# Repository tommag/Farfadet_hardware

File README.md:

# Farfadet Hardware

This repo contains KiCad EDA files for the Farfadet modular motor system.

You can check some info on the project here : <https://hackaday.io/project/45995-farfadet>

Each folder here contains a different hardware project. There is a schematic export in PDF format for each project. You can find the gerber files in the `gerber` directories. The Bill of Materials and component placement files are in the `production` directories. 

## License
This project is Open Source Hardware, licensed under the Creative Commons BY-SA 4.0 license. You can find the full license text here : <https://creativecommons.org/licenses/by-sa/4.0/>

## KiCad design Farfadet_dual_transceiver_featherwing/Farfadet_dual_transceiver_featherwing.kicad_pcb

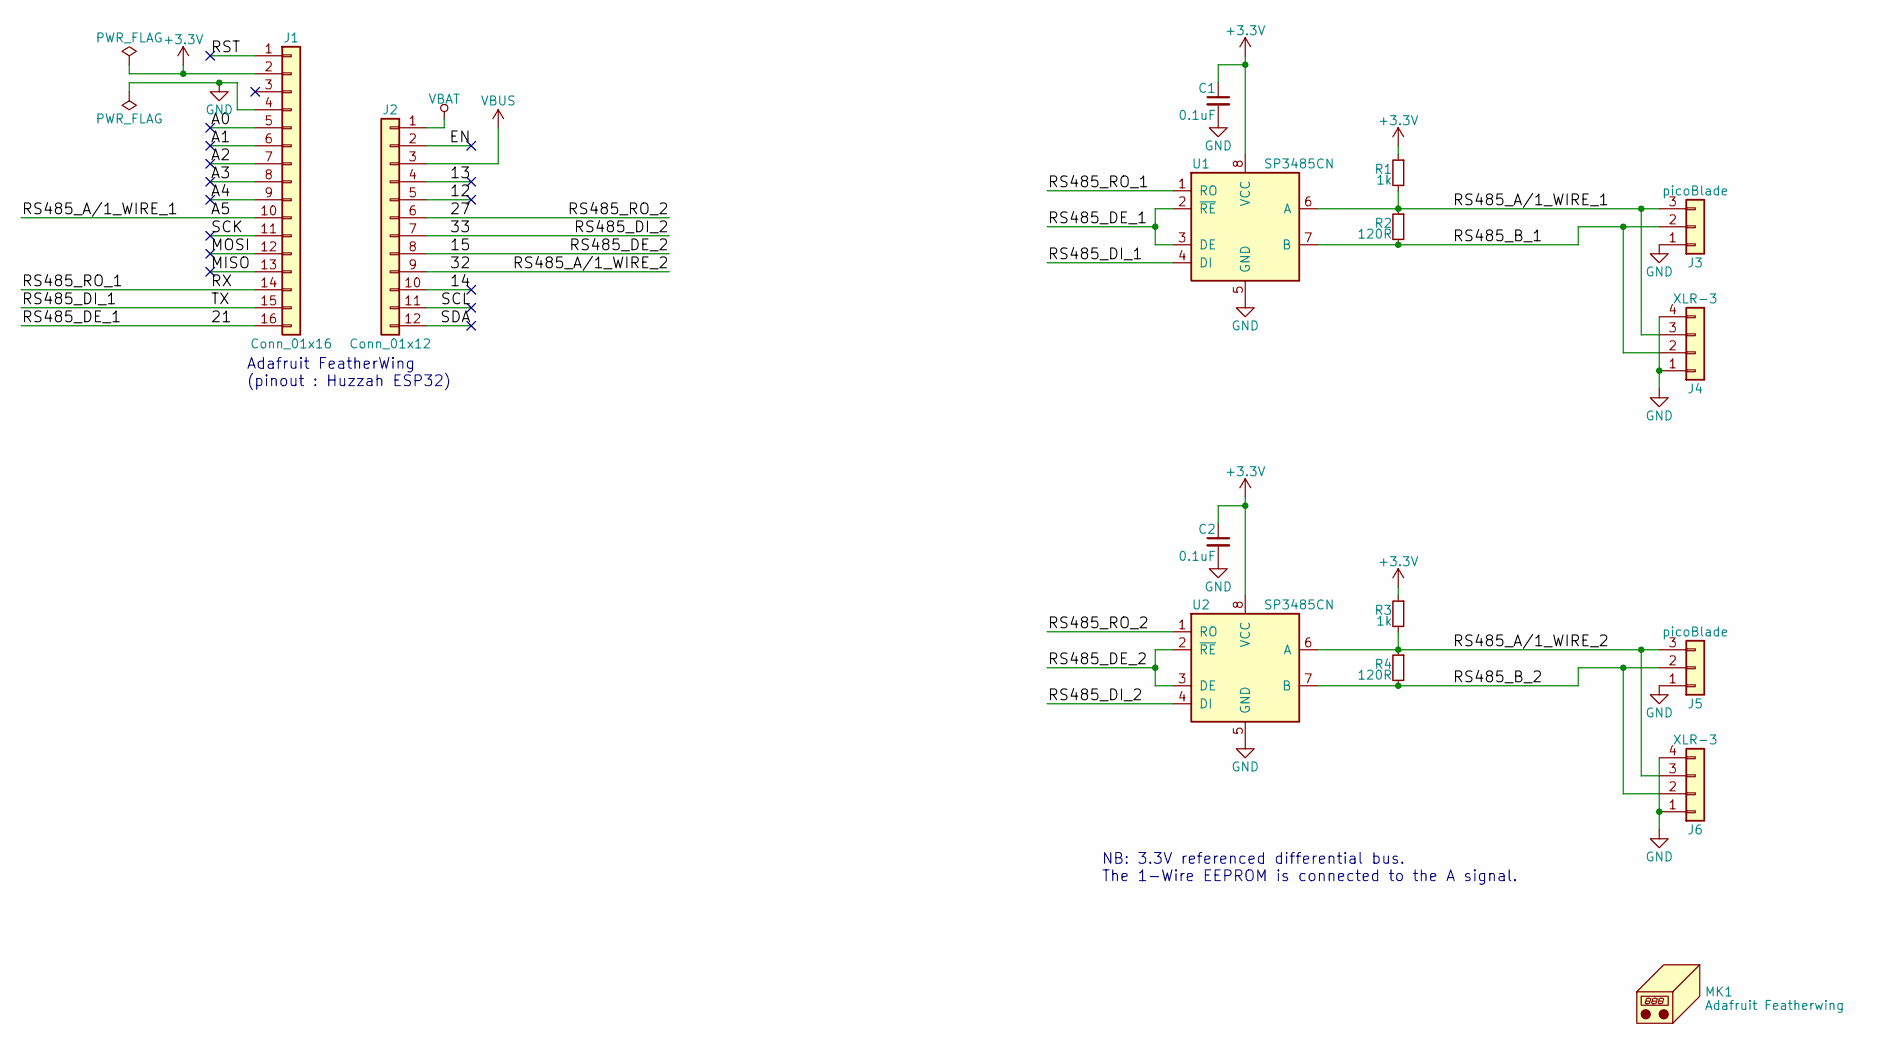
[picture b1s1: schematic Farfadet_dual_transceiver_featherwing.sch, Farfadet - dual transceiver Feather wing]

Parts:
C1, C2: 0.1uF; C_0603
J1: Conn_01x16; Pin_Header_Straight_1x16_Pitch2.54mm
J2: Conn_01x12; Pin_Header_Straight_1x12_Pitch2.54mm
J3, J5: picoBlade; Molex_PicoBlade_53047-0310_03x1.25mm_Straight
J4, J6: XLR-3; Neutrik_XLR_NC3FAAH2
MK1: Adafruit Featherwing; PCB_FeatherWing
R1, R3: 1k; R_0603
R2, R4: 120R; R_0603
U1, U2: SP3485CN; SOIC-8_3.9x4.9mm_Pitch1.27mm

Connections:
+3V3: C1.1, C2.1, J1.2, R1.1, R3.1, U1.8 (VCC), U2.8 (VCC)
/12: J2.5
/13: J2.4
/14: J2.10
/15: J2.8, U2.2 (~RE~), U2.3 (DE)
/21: J1.16, U1.2 (~RE~), U1.3 (DE)
/27: J2.6, U2.1 (RO)
/32: J2.9, J5.3, J6.3, R3.2, R4.1, U2.6 (A)
/33: J2.7, U2.4 (DI)
/A0: J1.5
/A1: J1.6
/A2: J1.7
/A3: J1.8
/A4: J1.9
/A5: J1.10, J3.3, J4.3, R1.2, R2.1, U1.6 (A)
/EN: J2.2
/MISO: J1.13
/MOSI: J1.12
/RS485_B_1: J3.2, J4.2, R2.2, U1.7 (B)
/RS485_B_2: J5.2, J6.2, R4.2, U2.7 (B)
/RS485_DI_1: J1.15, U1.4 (DI)
/RS485_RO_1: J1.14, U1.1 (RO)
/RST: J1.1
/SCK: J1.11
/SCL: J2.11
/SDA: J2.12
GND: C1.2, C2.2, J1.4, J3.1, J4.1, J4.4, J5.1, J6.1, J6.4, U1.5 (GND), U2.5 (GND)
VBAT: J2.1
VBUS: J2.3

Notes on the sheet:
Adafruit FeatherWing (pinout : Huzzah ESP32)
NB: 3.3V referenced differential bus. The 1-Wire EEPROM is connected to the A signal.

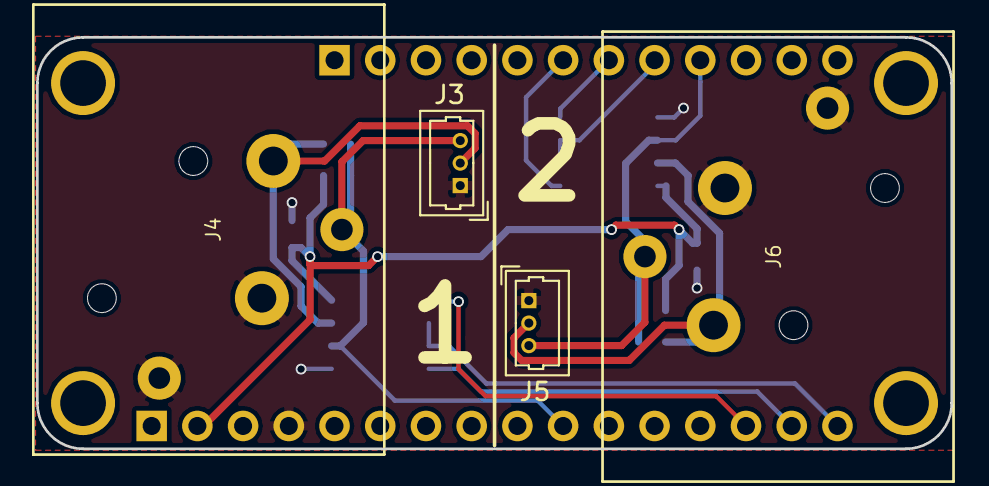
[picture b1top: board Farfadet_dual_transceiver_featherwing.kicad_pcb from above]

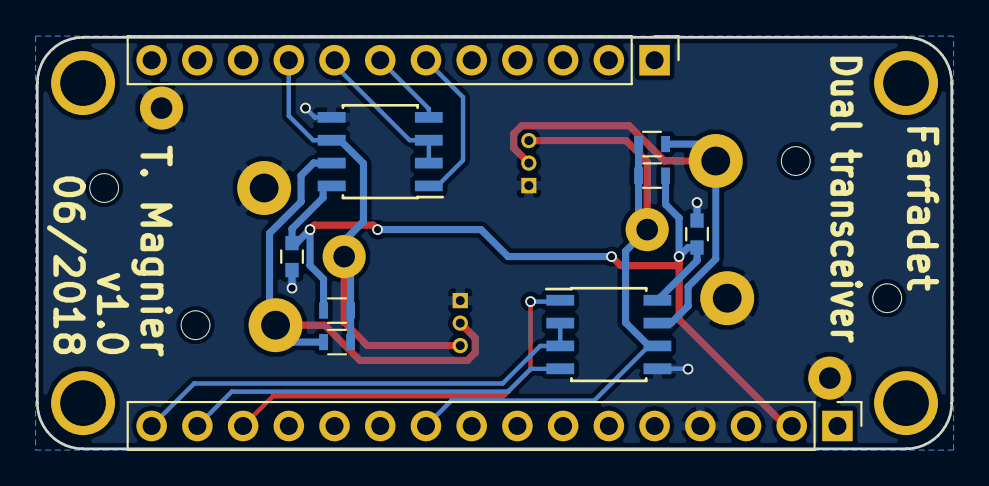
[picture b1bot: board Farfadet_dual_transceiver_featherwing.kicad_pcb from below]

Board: 2 copper layers, 50.8 x 22.9 mm, 15 parts (10 on the bottom side), 12 nets.

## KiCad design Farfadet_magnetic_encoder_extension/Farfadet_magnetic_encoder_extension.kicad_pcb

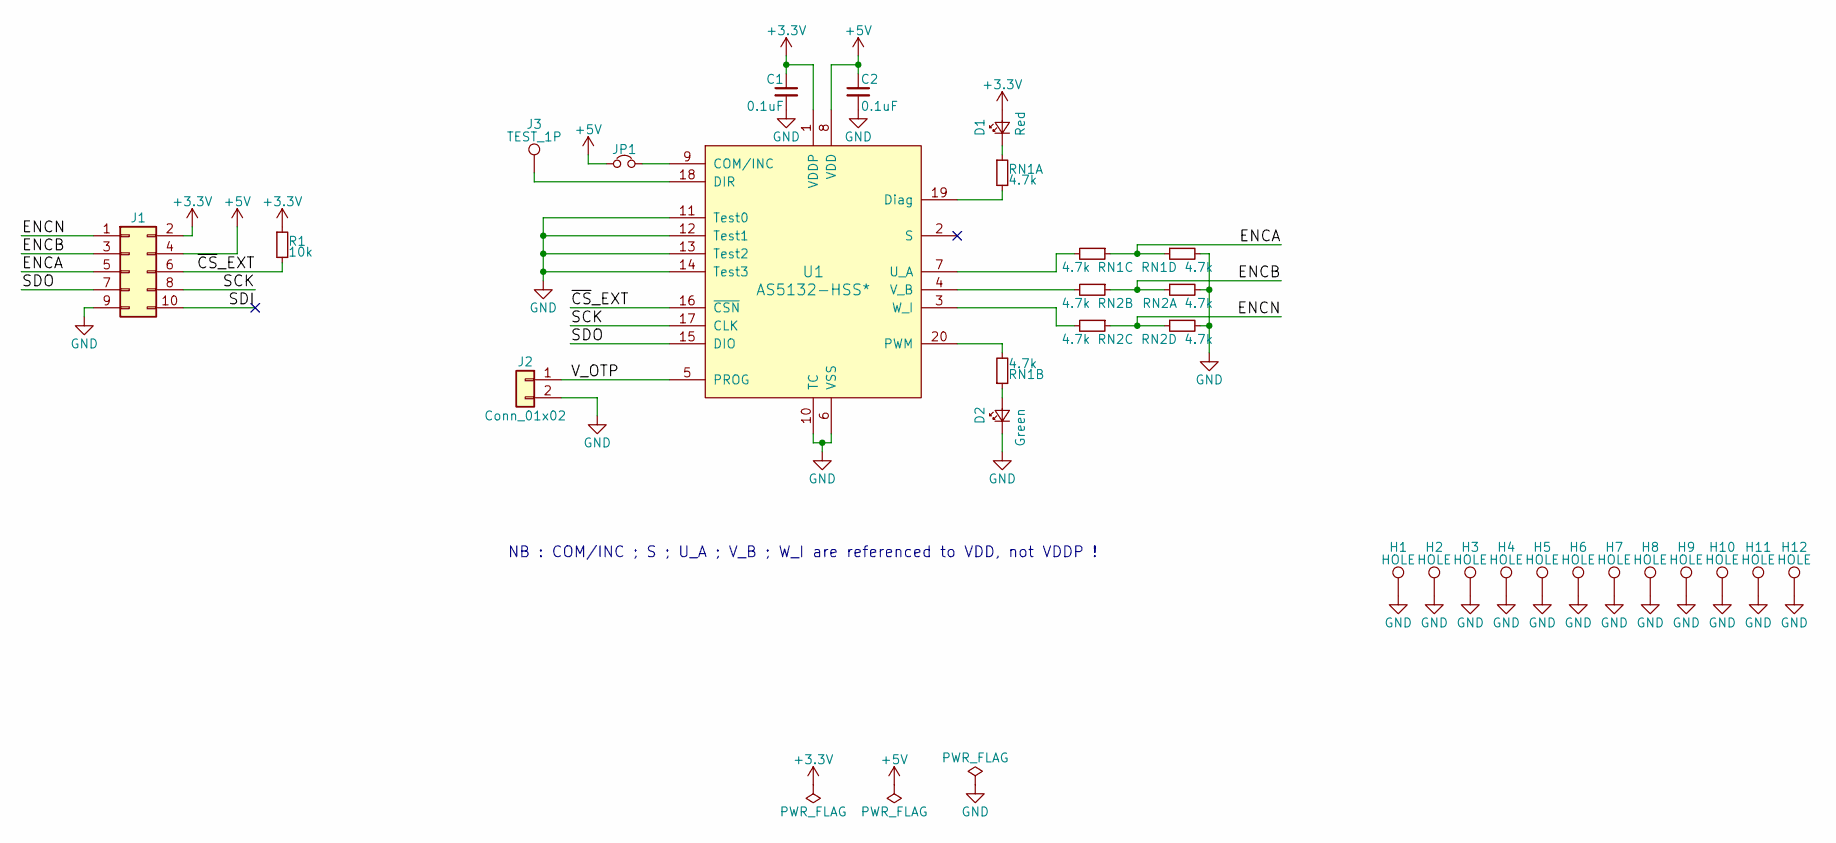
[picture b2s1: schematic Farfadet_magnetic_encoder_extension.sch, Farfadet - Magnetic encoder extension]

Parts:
C1, C2: 0.1uF; C_0603
D1: Red; LED_0603
D2: Green; LED_0603
H1, H2, H3, H4, H5, H6, H7, H8, H9, H10, H11, H12: HOLE; MountingHole_3.2mm_M3_Pad_Via
J1: Conn_02x05_Odd_Even; Socket_Strip_Straight_2x05_Pitch1.27mm_SMD
J2: Conn_01x02; Test_Point_2Pads
J3: TEST_1P; Measurement_Point_Round-TH_Small
JP1: Jumper_NC_Small; Solder_Jumper_2_conn
R1: 10k; R_0603
RN1, RN2: 4.7k; R_Array_Convex_4x0603
U1: AS5132-HSS*; SSOP-20_5.3x7.2mm_Pitch0.65mm

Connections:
+3V3: C1.1, D1.2 (A), J1.2, R1.1, U1.1 (VDDP)
+5V: C2.1, J1.4, JP1.1, U1.8 (VDD)
/ENCA: J1.5, RN1.3, RN1.4
/ENCB: J1.3, RN2.1, RN2.2
/ENCN: J1.1, RN2.3, RN2.4
/SCK: J1.8, U1.17 (CLK)
/SDI: J1.10
/SDO: J1.7, U1.15 (DIO)
/V_OTP: J2.1, U1.5 (PROG)
/~CS~_EXT: J1.6, R1.2, U1.16 (~CSN)
GND: C1.2, C2.2, D2.1 (K), H1.1, H2.1, H3.1, H4.1, H5.1, H6.1, H7.1, H8.1, H9.1, H10.1, H11.1, H12.1, J1.9, J2.2, RN1.5, RN2.5, RN2.8, U1.6 (VSS), U1.10 (TC), U1.11 (Test0), U1.12 (Test1), U1.13 (Test2), U1.14 (Test3)
unnamed: D1.1 (K), RN1.1
unnamed: D2.2 (A), RN1.2
unnamed: J3.1, U1.18 (DIR)
unnamed: JP1.2, U1.9 (COM/INC)
unnamed: RN1.6, U1.7 (U_A)
unnamed: RN1.7, U1.20 (PWM)
unnamed: RN1.8, U1.19 (Diag)
unnamed: RN2.6, U1.3 (W_I)
unnamed: RN2.7, U1.4 (V_B)

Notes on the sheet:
NB : COM/INC ; S ; U_A ; V_B ; W_I are referenced to VDD, not VDDP !

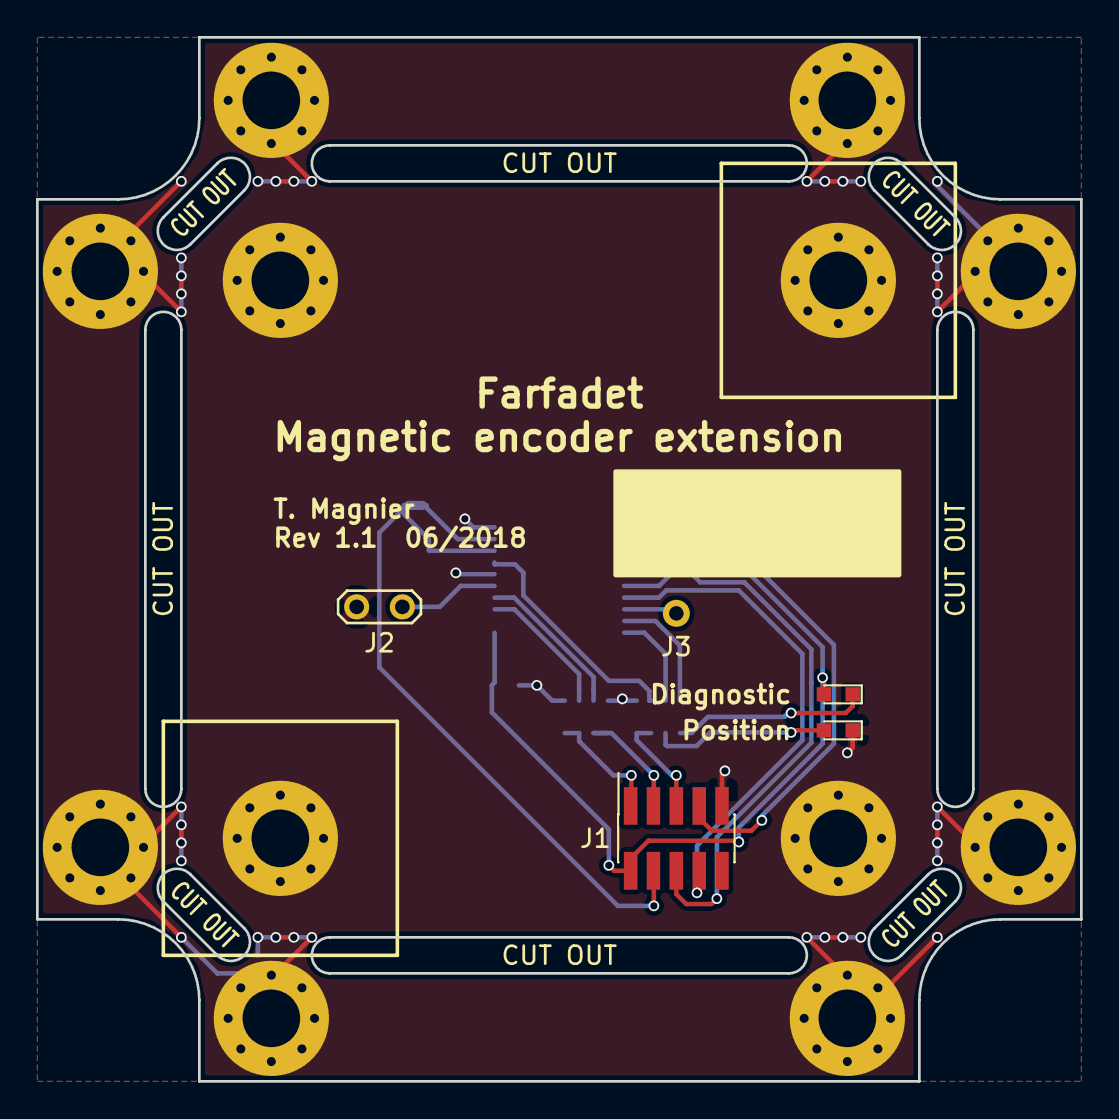
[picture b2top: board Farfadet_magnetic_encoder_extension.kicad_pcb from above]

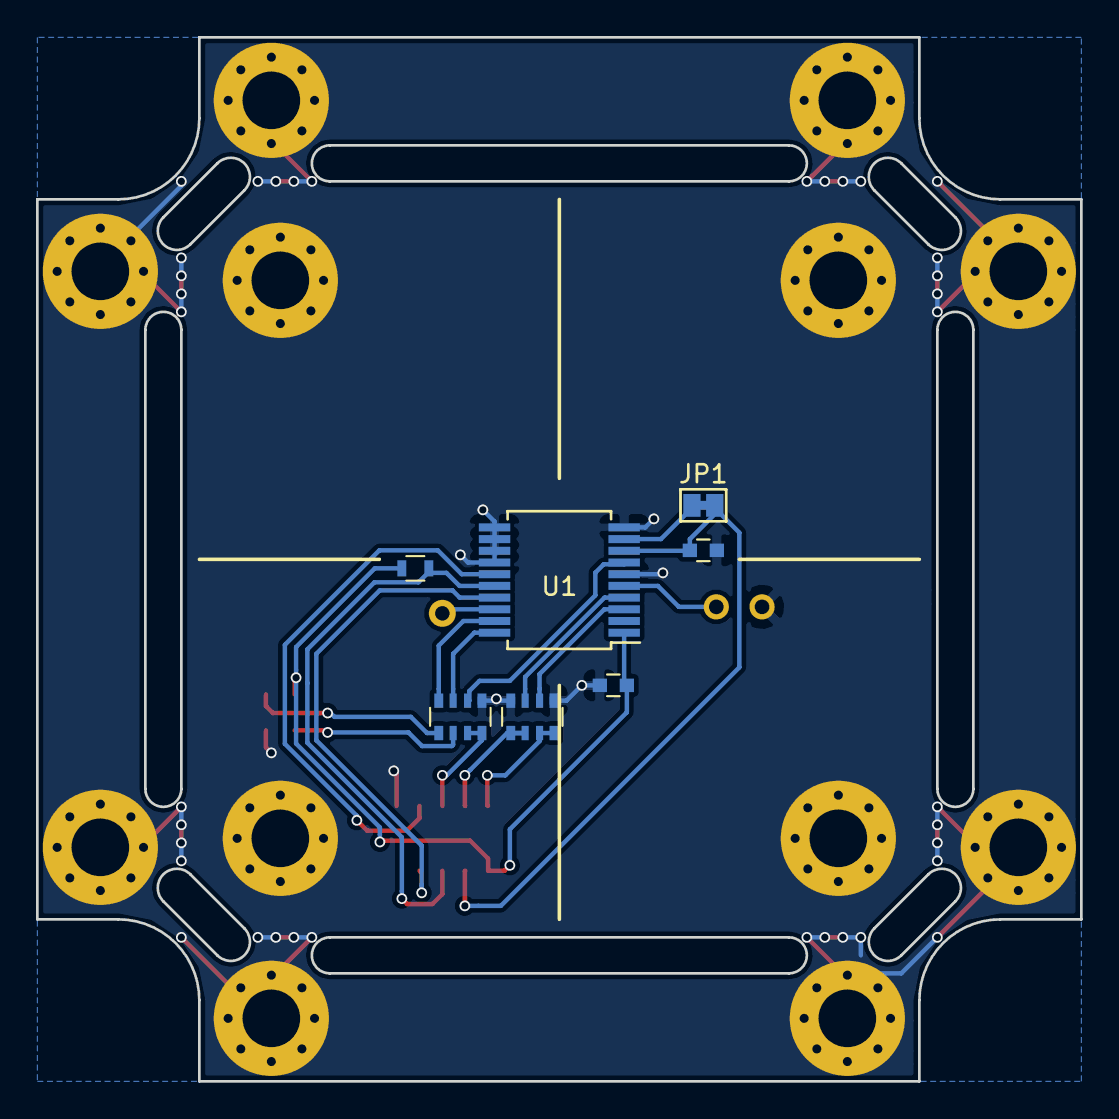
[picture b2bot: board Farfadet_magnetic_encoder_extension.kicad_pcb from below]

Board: 2 copper layers, 58.0 x 58.0 mm, 24 parts (7 on the bottom side), 19 nets.

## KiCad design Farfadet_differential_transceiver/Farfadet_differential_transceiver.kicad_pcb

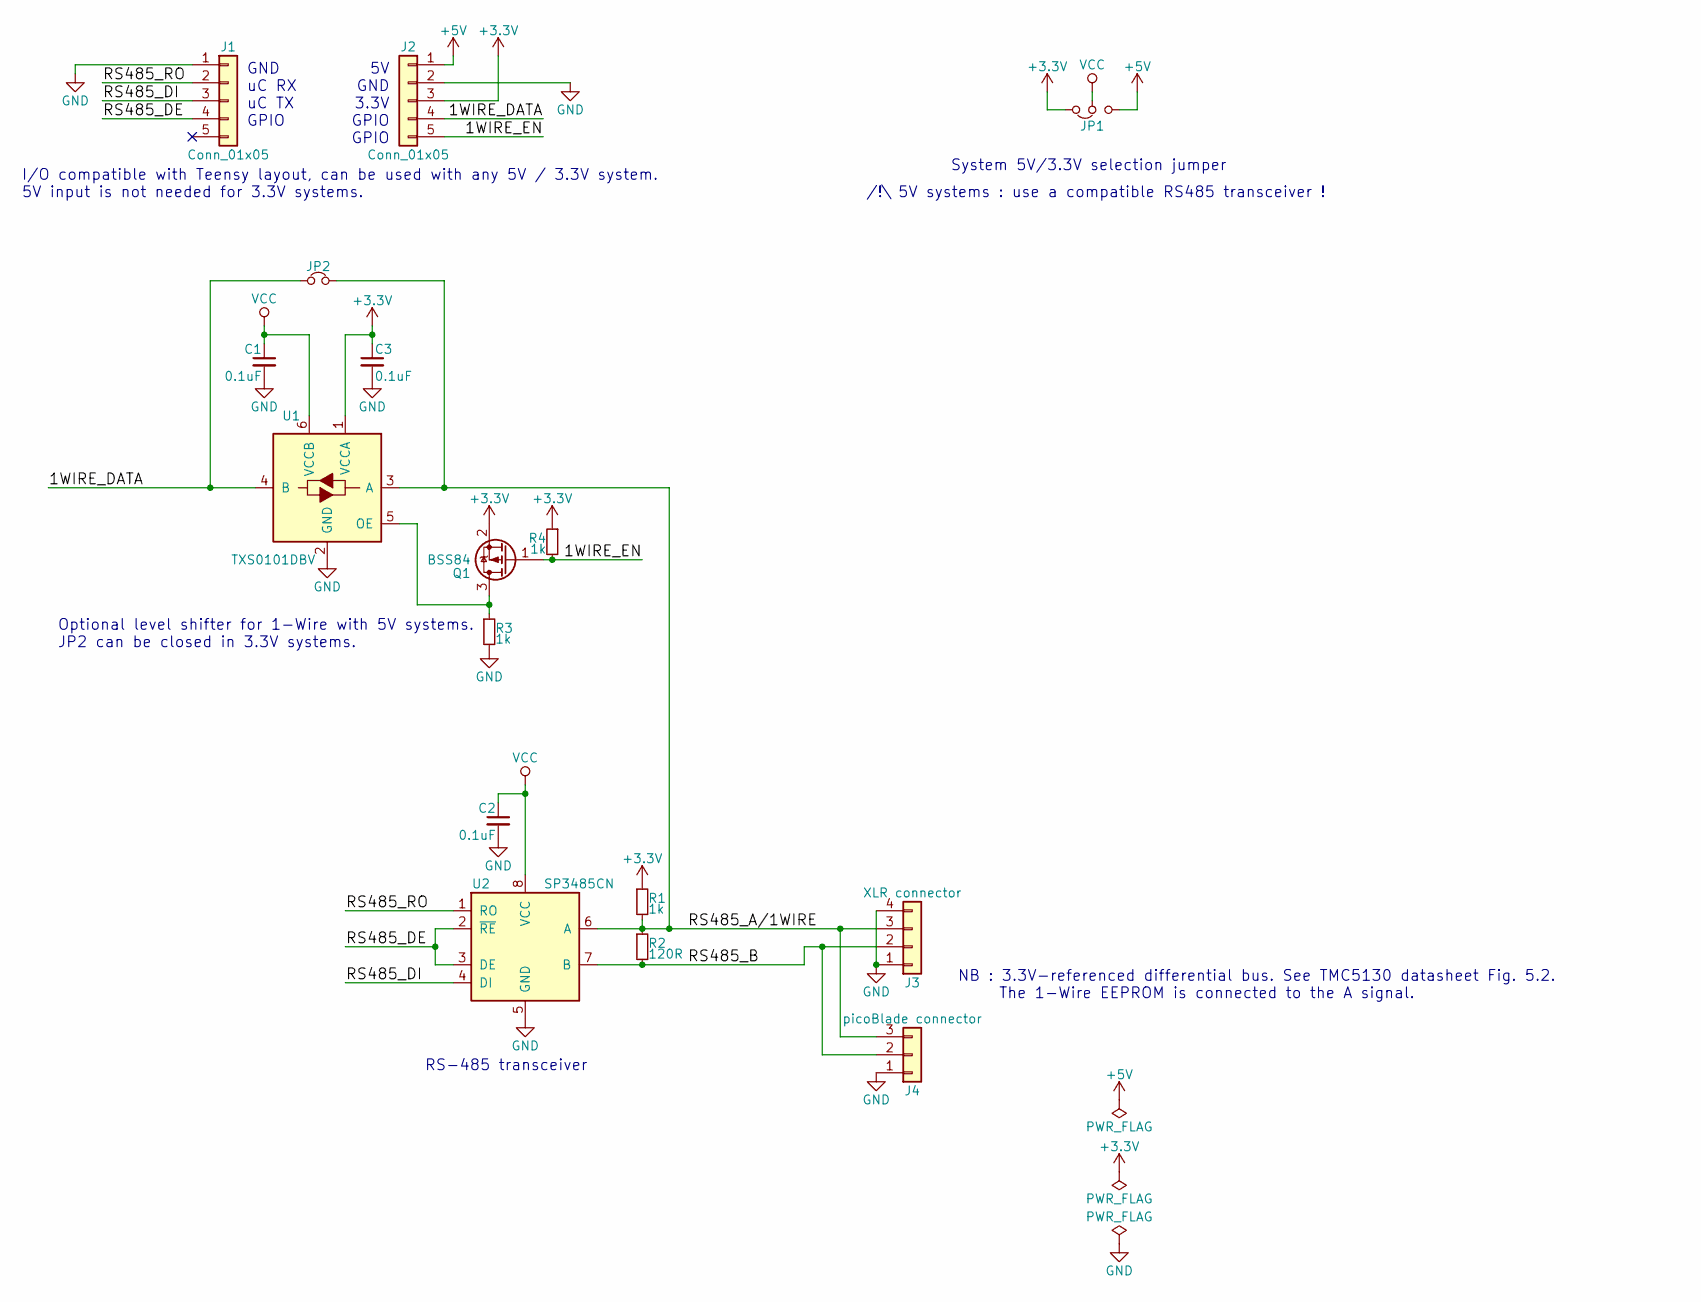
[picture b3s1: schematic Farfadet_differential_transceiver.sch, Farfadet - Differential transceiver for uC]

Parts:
C1, C2, C3: 0.1uF; C_0603
J1, J2: Conn_01x05; Pin_Header_Straight_1x05_Pitch2.54mm
J3: XLR connector; Neutrik_XLR_NC3FAAH2
J4: picoBlade connector; Molex_PicoBlade_53047-0310_03x1.25mm_Straight
JP1: Jumper_Dual_NC_NO_Small; Solder_Jumper_3_conn_1-2
JP2: Jumper_NC_Small; Solder_Jumper_2_conn
Q1: BSS84; SOT-23
R1, R3, R4: 1k; R_0603
R2: 120R; R_0603
U1: TXS0101DBV; SOT-23-6
U2: SP3485CN; SOIC-8_3.9x4.9mm_Pitch1.27mm

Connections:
+3V3: C3.1, J2.3, JP1.1, Q1.2 (S), R1.1, R4.1, U1.1 (VCCA)
+5V: J2.1, JP1.3
/1WIRE_DATA: J2.4, JP2.1, U1.4 (B)
/1WIRE_EN: J2.5, Q1.1 (G), R4.2
/RS485_A/1WIRE: J3.3, J4.3, JP2.2, R1.2, R2.1, U1.3 (A), U2.6 (A)
/RS485_B: J3.2, J4.2, R2.2, U2.7 (B)
/RS485_DE: J1.4, U2.2 (~RE~), U2.3 (DE)
/RS485_DI: J1.3, U2.4 (DI)
/RS485_RO: J1.2, U2.1 (RO)
GND: C1.2, C2.2, C3.2, J1.1, J2.2, J3.1, J3.4, J4.1, R3.2, U1.2 (GND), U2.5 (GND)
unnamed: Q1.3 (D), R3.1, U1.5 (OE)
VCC: C1.1, C2.1, JP1.2, U1.6 (VCCB), U2.8 (VCC)

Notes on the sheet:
I/O compatible with Teensy layout, can be used with any 5V / 3.3V system. 5V input is not needed for 3.3V systems.
GND uC RX uC TX GPIO
5V GND 3.3V GPIO GPIO
System 5V/3.3V selection jumper
/!\ 5V systems : use a compatible RS485 transceiver !
NB : 3.3V-referenced differential bus. See TMC5130 datasheet Fig. 5.2. The 1-Wire EEPROM is connected to the A signal.
RS-485 transceiver
Optional level shifter for 1-Wire with 5V systems. JP2 can be closed in 3.3V systems.

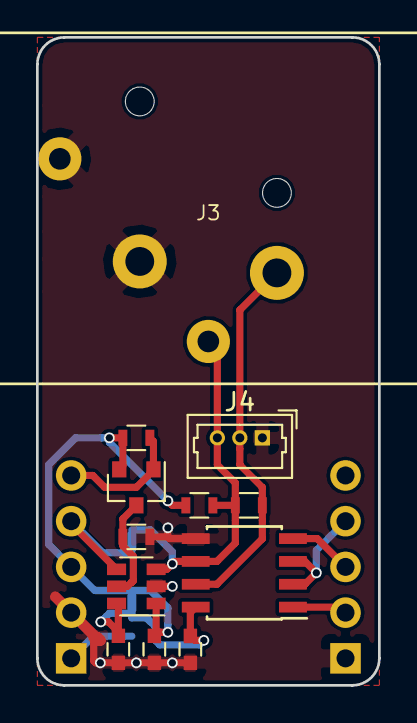
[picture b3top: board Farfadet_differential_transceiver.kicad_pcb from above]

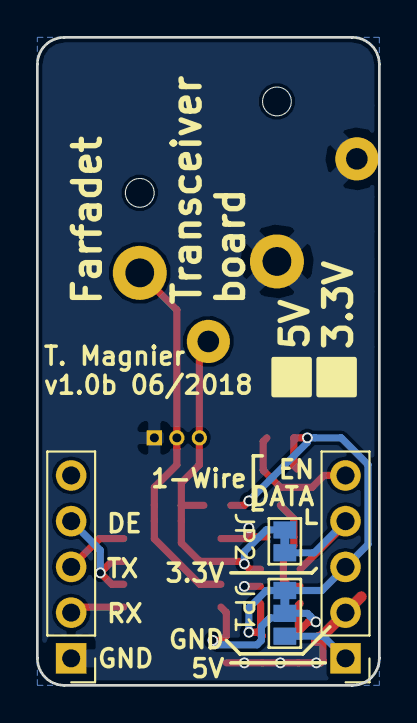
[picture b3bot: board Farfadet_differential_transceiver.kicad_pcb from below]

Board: 2 copper layers, 19.0 x 36.0 mm, 16 parts (4 on the bottom side), 12 nets.

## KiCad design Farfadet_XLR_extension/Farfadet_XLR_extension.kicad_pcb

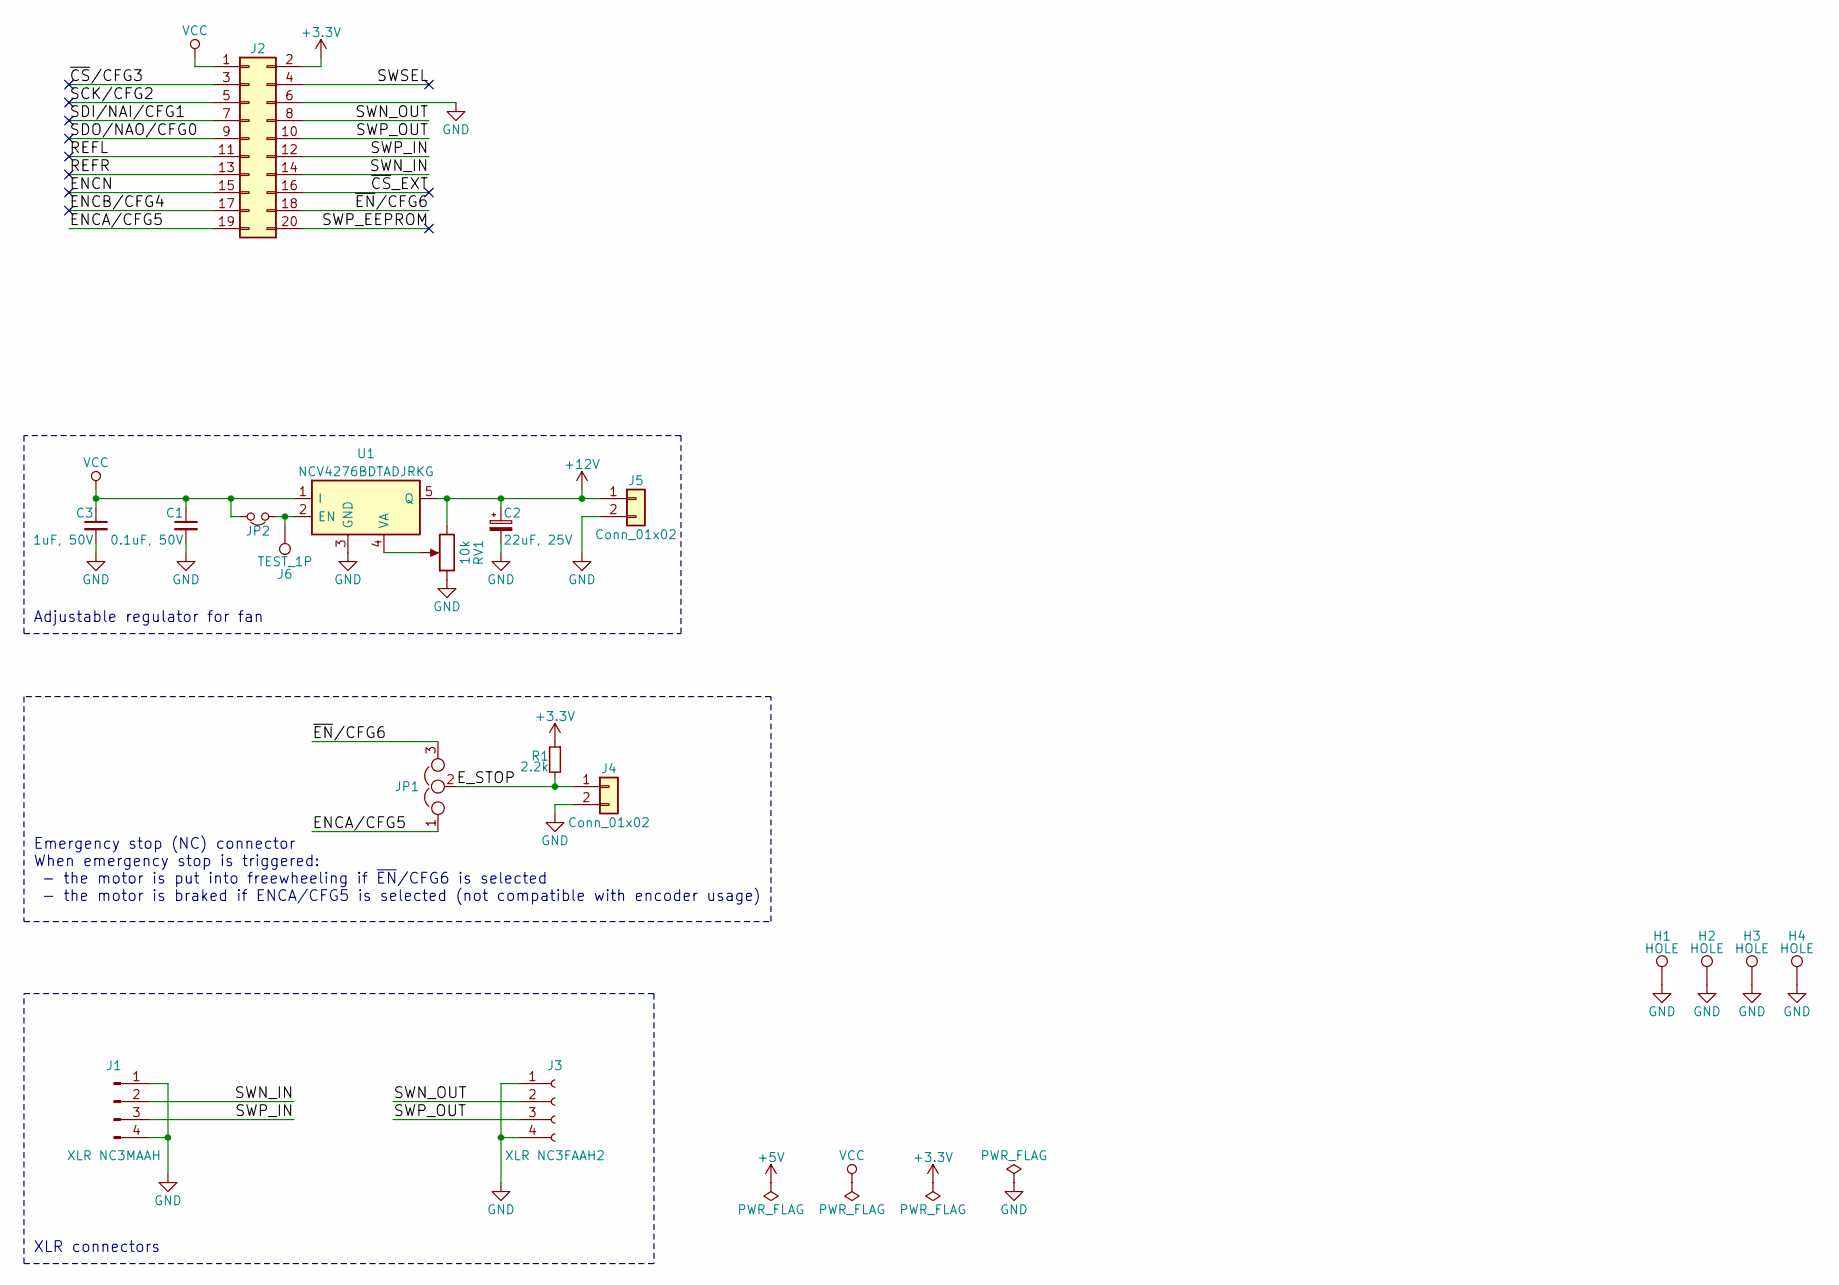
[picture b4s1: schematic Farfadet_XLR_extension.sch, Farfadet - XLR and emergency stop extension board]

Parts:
C1: 0.1uF, 50V; C_0603
C2: 22uF, 25V; CP_Elec_6.3x4.5
C3: 1uF, 50V; C_0805
H1, H2, H3, H4: HOLE; MountingHole_3.2mm_M3_Pad_Via
J1: XLR NC3MAAH; Neutrik_XLR_NC3MAAH
J2: Conn_02x10_Odd_Even; Socket_Strip_Straight_2x10_Pitch1.27mm_SMD
J3: XLR NC3FAAH2; Neutrik_XLR_NC3FAAH2
J4: Conn_01x02; TerminalBlock_Pheonix_MPT-2.54mm_2pol
J5: Conn_01x02; JST_PH_B2B-PH-K_02x2.00mm_Straight
J6: TEST_1P; PINTST
JP1: Jumper_NC_Dual; Solder_Jumper_3_open
JP2: Jumper_NC_Small; Solder_Jumper_2_conn
R1: 2.2k; R_0603
RV1: 10k; Potentiometer_Trimmer-EVM3E
U1: NCV4276BDTADJRKG; TO-252-4

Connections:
+3V3: J2.2, R1.1
+12V: C2.1, J5.1, RV1.3, U1.5 (Q)
/ENCA/CFG5: J2.19, JP1.1
/ENCB/CFG4: J2.17
/ENCN: J2.15
/E_STOP: J4.1, JP1.2, R1.2
/REFL: J2.11
/REFR: J2.13
/SCK/CFG2: J2.5
/SDI/NAI/CFG1: J2.7
/SDO/NAO/CFG0: J2.9
/SWN_IN: J1.2, J2.14
/SWN_OUT: J2.8, J3.2
/SWP_EEPROM: J2.20
/SWP_IN: J1.3, J2.12
/SWP_OUT: J2.10, J3.3
/SWSEL: J2.4
/~CS~/CFG3: J2.3
/~CS~_EXT: J2.16
/~EN~/CFG6: J2.18, JP1.3
GND: C1.2, C2.2, C3.2, H1.1, H2.1, H3.1, H4.1, J1.1, J1.4, J2.6, J3.1, J3.4, J4.2, J5.2, RV1.1, U1.3 (GND)
unnamed: J6.1, JP2.2, U1.2 (EN)
unnamed: RV1.2, U1.4 (VA)
VCC: C1.1, C3.1, J2.1, JP2.1, U1.1 (I)

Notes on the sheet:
XLR connectors
Emergency stop (NC) connector When emergency stop is triggered: - the motor is put into freewheeling if ~EN~/CFG6 is selected - the motor is braked if ENCA/CFG5 is selected (not compatible with encoder usage)
Adjustable regulator for fan

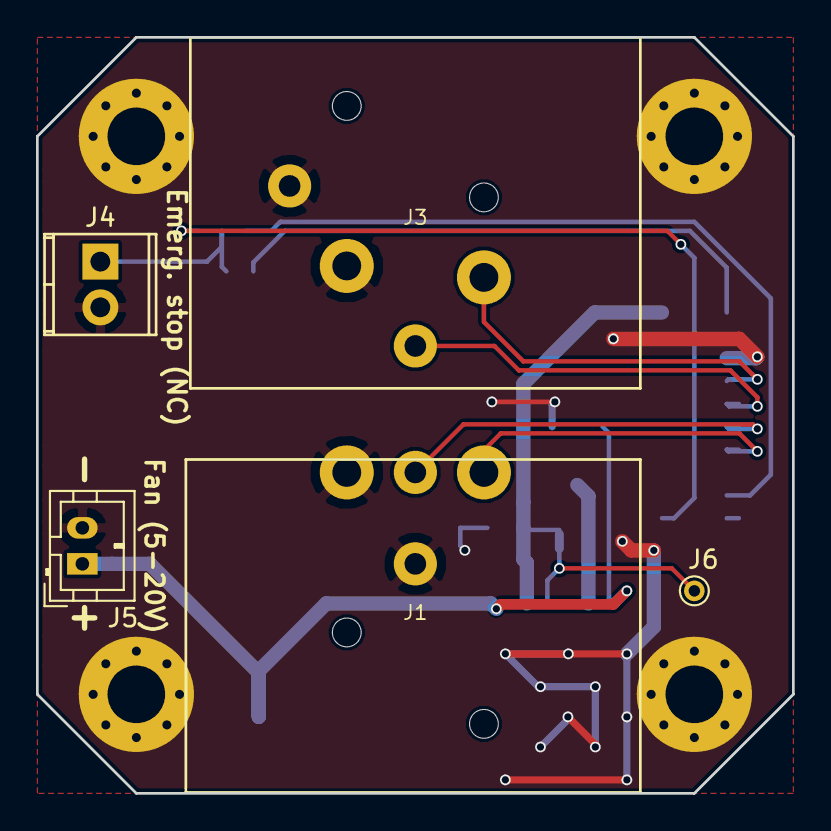
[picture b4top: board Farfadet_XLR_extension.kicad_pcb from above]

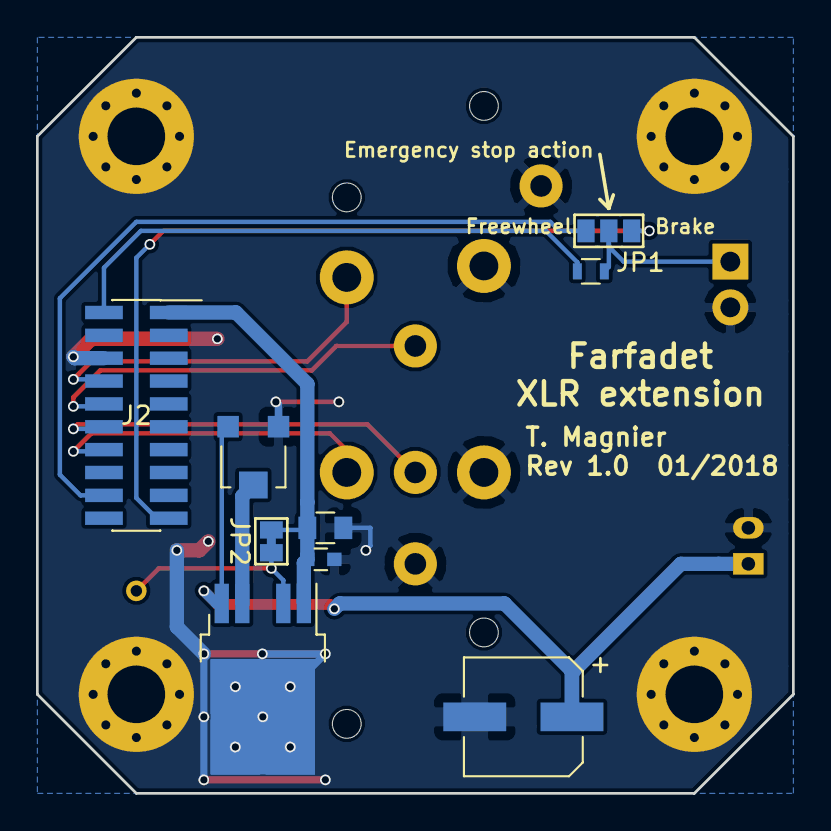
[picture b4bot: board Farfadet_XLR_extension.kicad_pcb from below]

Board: 2 copper layers, 42.0 x 42.0 mm, 18 parts (9 on the bottom side), 13 nets.

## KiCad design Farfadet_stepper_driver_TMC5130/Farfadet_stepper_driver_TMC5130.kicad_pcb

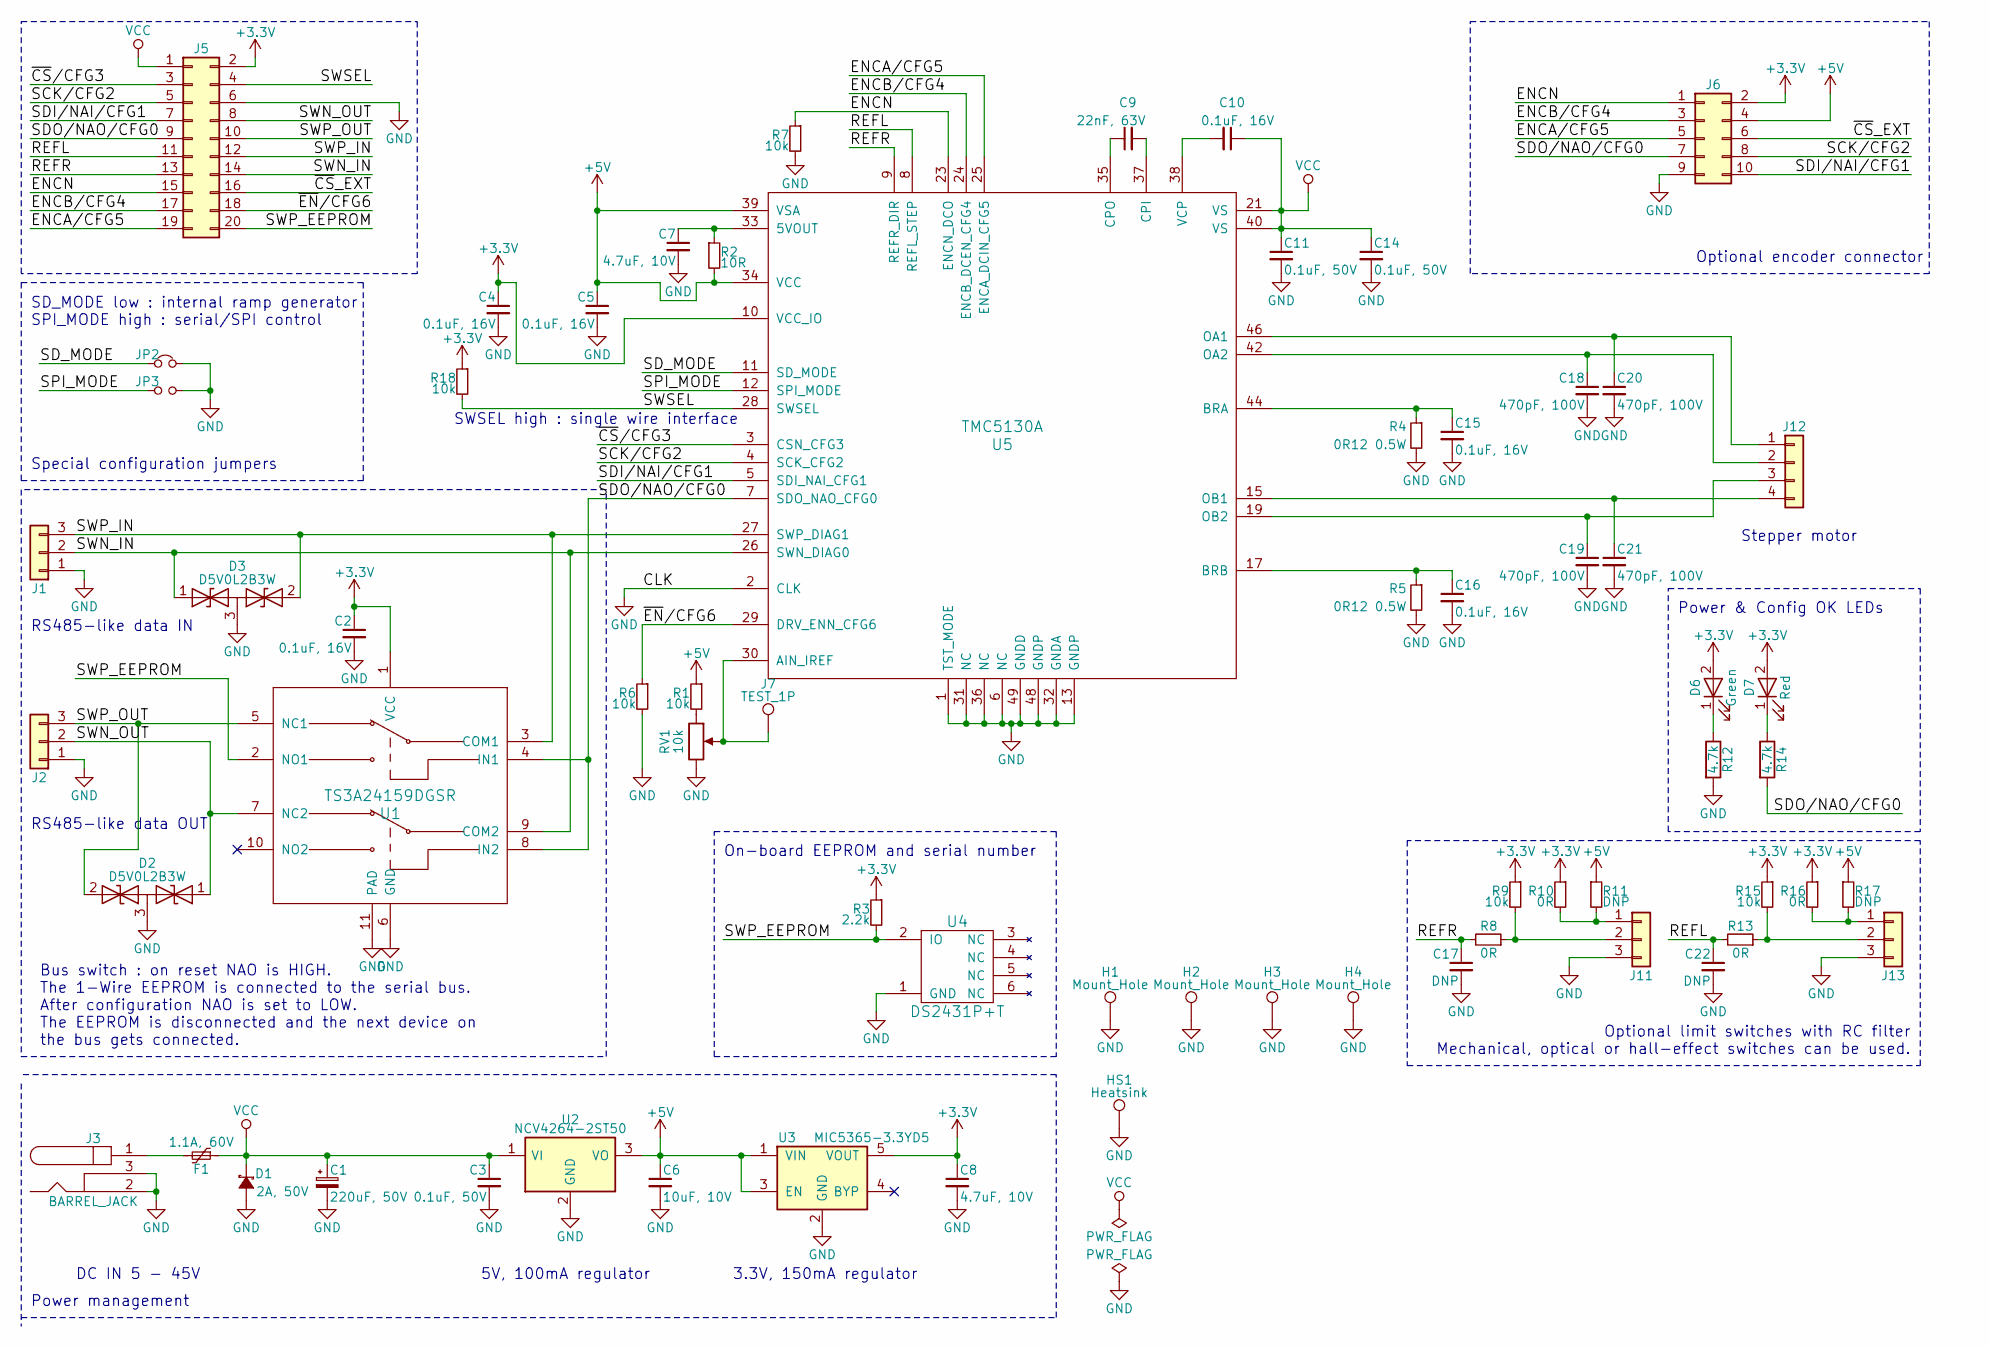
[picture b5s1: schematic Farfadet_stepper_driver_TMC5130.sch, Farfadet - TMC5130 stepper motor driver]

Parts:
C1: 220uF, 50V; CP_Elec_8x10.5
C2, C4, C5, C10, C15, C16: 0.1uF, 16V; C_0603
C3, C11, C14: 0.1uF, 50V; C_0603
C6: 10uF, 10V; C_0805
C7, C8: 4.7uF, 10V; C_0805
C9: 22nF, 63V; C_0603
C17, C22: DNP; C_0603
C18, C19, C20, C21: 470pF, 100V; C_0603
D1: 2A, 50V; D_SMA
D2, D3: D5V0L2B3W; SOT-323_SC-70
D6: Green; LED_0603
D7: Red; LED_0603
F1: 1.1A, 60V; Fuse_SMD2920
H1, H2, H3, H4: Mount_Hole; MountingHole_3.2mm_M3_Pad_Via
HS1: Heatsink; Heatsink_Adhesive_10x10mm
J1, J2, J11, J13: Conn_01x03; Molex_PicoBlade_53261-0371_03x1.25mm_Angled
J3: BARREL_JACK; JACK_ALIM
J5: Conn_02x10_Odd_Even; Pin_Header_Straight_2x10_Pitch1.27mm_SMD
J6: Conn_02x05_Odd_Even; Pin_Header_Straight_2x05_Pitch1.27mm_SMD
J7: TEST_1P; Measurement_Point_Round-TH_Small
J12: Conn_01x04; TerminalBlock_Pheonix_MPT-2.54mm_4pol
JP2: Jumper_NC_Small; Solder_Jumper_2_conn
JP3: Jumper_NO_Small; Solder_Jumper_2_open
R1, R6, R7, R9, R15, R18: 10k; R_0603
R2: 10R; R_0603
R3: 2.2k; R_0603
R4, R5: 0R12 0.5W; R_1206
R8, R10, R13, R16: 0R; R_0603
R11, R17: DNP; R_0603
R12, R14: 4.7k; R_0603
RV1: 10k; Potentiometer_Trimmer-EVM3E
U1: TS3A24159DGSR; TSSOP-10_3x3mm_Pitch0.5mm
U2: NCV4264-2ST50; SOT-223-3Lead_TabPin2
U3: MIC5365-3.3YD5; SOT-23-5
U4: DS2431P+T; TSOC-6_4x3.8mm_Pitch1.27mm
U5: TMC5130A; TQFP-48-1EP_7x7mm_Pitch0.5mm

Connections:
+3V3: C2.1, C4.1, C8.1, D6.2 (A), D7.2 (A), J5.2, J6.2, R3.1, R9.1, R10.1, R15.1, R16.1, R18.1, U1.1 (VCC), U3.5 (VOUT), U5.10 (VCC_IO)
+5V: C5.1, C6.1, J6.4, R1.1, R2.2, R11.1, R17.1, U2.3 (VO), U3.1 (VIN), U3.3 (EN), U5.34 (VCC), U5.39 (VSA)
/ENCA/CFG5: J5.19, J6.5, U5.25 (ENCA_DCIN_CFG5)
/ENCB/CFG4: J5.17, J6.3, U5.24 (ENCB_DCEN_CFG4)
/ENCN: J5.15, J6.1, R7.1, U5.23 (ENCN_DCO)
/REFL: C22.1, J5.11, R13.2, U5.8 (REFL_STEP)
/REFR: C17.1, J5.13, R8.2, U5.9 (REFR_DIR)
/SCK/CFG2: J5.5, J6.8, U5.4 (SCK_CFG2)
/SDI/NAI/CFG1: J5.7, J6.10, U5.5 (SDI_NAI_CFG1)
/SDO/NAO/CFG0: J5.9, J6.7, R14.2, U1.4 (IN1), U1.8 (IN2), U5.7 (SDO_NAO_CFG0)
/SD_MODE: JP2.1, U5.11 (SD_MODE)
/SPI_MODE: JP3.1, U5.12 (SPI_MODE)
/SWN_IN: D3.1 (A1), J1.2, J5.14, U1.9 (COM2), U5.26 (SWN_DIAG0)
/SWN_OUT: D2.1 (A1), J2.2, J5.8, U1.7 (NC2)
/SWP_EEPROM: J5.20, R3.2, U1.2 (NO1), U4.2 (IO)
/SWP_IN: D3.2 (A2), J1.3, J5.12, U1.3 (COM1), U5.27 (SWP_DIAG1)
/SWP_OUT: D2.2 (A2), J2.3, J5.10, U1.5 (NC1)
/SWSEL: J5.4, R18.2, U5.28 (SWSEL)
/~CS~/CFG3: J5.3, U5.3 (CSN_CFG3)
/~CS~_EXT: J5.16, J6.6
/~EN~/CFG6: J5.18, R6.1, U5.29 (DRV_ENN_CFG6)
GND: C1.2, C2.2, C3.2, C4.2, C5.2, C6.2, C7.2, C8.2, C11.2, C14.2, C15.2, C16.2, C17.2, C18.2, C19.2, C20.2, C21.2, C22.2, D1.2 (A), D2.3 (common), D3.3 (common), H1.1, H2.1, H3.1, H4.1, HS1.1, J1.1, J2.1, J3.2, J3.3, J5.6, J6.9, J11.3, J13.3, JP2.2, JP3.2, R4.2, R5.2, R6.2, R7.2, R12.2, RV1.3, U1.6 (GND), U1.11 (PAD), U2.2 (GND), U3.2 (GND), U4.1 (GND), U5.1 (TST_MODE), U5.2 (CLK), U5.6 (NC), U5.13 (GNDP), U5.31 (NC), U5.32 (GNDA), U5.36 (NC), U5.48 (GNDP), U5.49 (GNDD)
unnamed: C7.1, R2.1, U5.33 (5VOUT)
unnamed: C9.1, U5.35 (CPO)
unnamed: C9.2, U5.37 (CPI)
unnamed: C10.2, U5.38 (VCP)
unnamed: C15.1, R4.1, U5.44 (BRA)
unnamed: C16.1, R5.1, U5.17 (BRB)
unnamed: C18.1, J12.2, U5.42 (OA2)
unnamed: C19.1, J12.3, U5.19 (OB2)
unnamed: C20.1, J12.1, U5.46 (OA1)
unnamed: C21.1, J12.4, U5.15 (OB1)
unnamed: D6.1 (K), R12.1
unnamed: D7.1 (K), R14.1
unnamed: F1.2, J3.1
unnamed: J7.1, RV1.2, U5.30 (AIN_IREF)
unnamed: J11.1, R10.2, R11.2
unnamed: J11.2, R8.1, R9.2
unnamed: J13.1, R16.2, R17.2
unnamed: J13.2, R13.1, R15.2
unnamed: R1.2, RV1.1
VCC: C1.1, C3.1, C10.1, C11.1, C14.1, D1.1 (K), F1.1, J5.1, U2.1 (VI), U5.21 (VS), U5.40 (VS)

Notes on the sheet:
Stepper motor
DC IN 5 - 45V
RS485-like data IN
RS485-like data OUT
5V, 100mA regulator
3.3V, 150mA regulator
Bus switch : on reset NAO is HIGH. The 1-Wire EEPROM is connected to the serial bus. After configuration NAO is set to LOW. The EEPROM is disconnected and the next device on the bus gets connected.
Power management
On-board EEPROM and serial number
Power & Config OK LEDs
Optional limit switches with RC filter Mechanical, optical or hall-effect switches can be used.
SD_MODE low : internal ramp generator SPI_MODE high : serial/SPI control
Optional encoder connector
SWSEL high : single wire interface
Special configuration jumpers
